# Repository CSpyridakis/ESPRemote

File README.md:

# ESPRemote
### VER 1.1

This repository is a fork of [Almidi's version of ESPRemote](https://github.com/Almidi/ESPRemote), a simple WiFI remote controller using the ESP8266 SoC.

The main difference between his implementation and this fork is about the limit of the input power supply voltage. In his repo, he uses an _[AP2112K](https://www.google.gr/url?sa=t&rct=j&q=&esrc=s&source=web&cd=1&ved=2ahUKEwjnxLrnpvbgAhUEK1AKHWMBD-AQFjAAegQIChAC&url=https%3A%2F%2Fwww.diodes.com%2Fassets%2FDatasheets%2FAP2112.pdf&usg=AOvVaw2XV2W1VE0JfD3LlF0lkARI)_ LDO voltage regulator that has a 6.5V Vin limit, to power it from USB chargers. 

Personally, I have all over in my place 12V power supplies to power led strips, for this reason, it would be a nice touch if I could power it directly from there without the need for an external power supply. So in this fork, the [NCP1117](https://www.onsemi.com/pub/Collateral/NCP1117-D.PDF) or [AMS1117](http://www.advanced-monolithic.com/pdf/ds1117.pdf) voltage regulator is used.

Please check out his [repo](https://github.com/Almidi/ESPRemote) if you want to use the battery/5v dc version, learn more about the beginning version or details about the firmware.

## PCB
### Schematic

#### Note: C3, C4, C5 and C6 are optional !!!

### Assembly
| No  |   Component   |    Quantity      |
|:---:|:-------------:|:----------------:|
| 1.  |      ESP8266 - 12e/f         | 1 | 
| 2.  |    10KΩ 0805 smd resistors   | 9 | 
| 3.  |      SMD-SWITCH-6.2MM        | 5 |
| 4.  |  IN5819 or SS14 or S4 Diode  | 1 |
| 5.  | NCP1117 or REG1117 Regulator | 1 |
| 6.  | 10uF 25v 0805 smd capasitors | 2 |
| 7.  |          0603 smd led        | 1 |
| 8.  |  0805 smd resistor for led <sup>1</sup>  | 1 |

<sup>1</sup> The resistor value depends on the color of the led you would choose to use.

### Top

### Bottom

## I/O

| Usage           | Pin    |
|-----------------|--------|
| Button 1        | GPIO5  |
| Button 2        | GPIO4  |
| Button 3        | GPIO12 |
| Button 4        | GPIO0  |
| Button 5        | GPIO13 |
| Status Led      | GPIO16 |

## Enclosure 
I also use [Almidi's](https://github.com/Almidi/ESPRemote) enclosure for this version.

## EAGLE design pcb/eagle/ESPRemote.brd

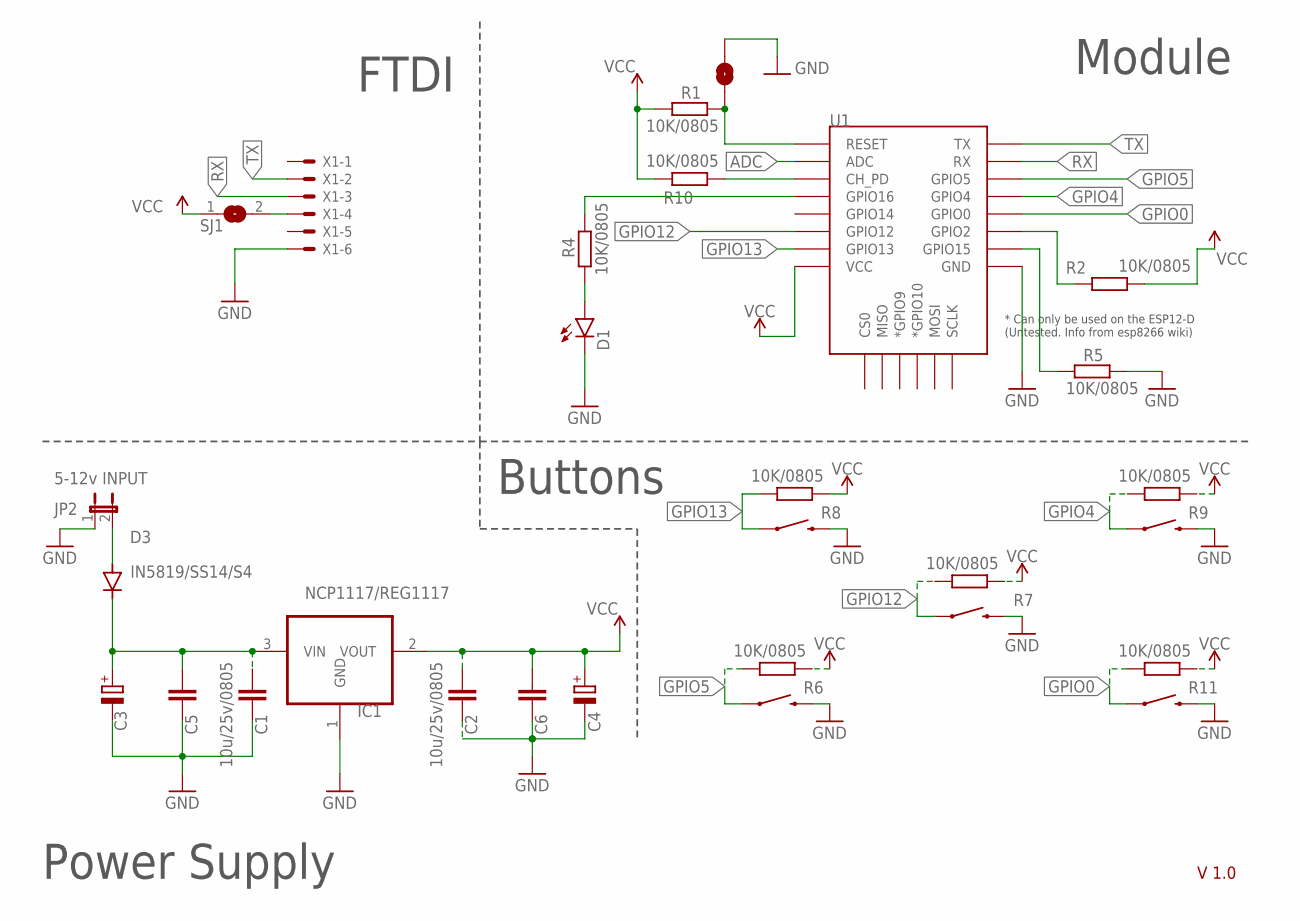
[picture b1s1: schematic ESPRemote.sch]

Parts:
C1, C2, C5, C6: 10u/25v/0805; C0805
C3, C4: CPOL-EUE2-5; E2-5
D1: BLUE; CHIP-LED0805
D3: IN5819/SS14/S4; DO-214AC
IC1: NCP1117/REG1117; SOT223
JP1: RST; SMT-JUMPER_2_NO_NO-SILK
JP2: 5-12v INPUT; JP1
R1, R2, R4, R5, R6, R7, R8, R9, R10, R11: 10K/0805; R0805
S0, S1, S2, S3, S4: SMD-SWITCH-6.2MM; TACTILE_SWITCH_SMD_6.0X3.5MM
SJ1: SJ
U1: ESP12ESMD; ESP12E-SMD
X1: JST-XH-06-PIN-ROUND-PAD; JST-XH-06-PACKAGE-ROUND-PAD

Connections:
ADC: U1.ADC
GND: C1.1, C2.1, C3.-, C4.-, C5.1, C6.1, D1.C, IC1.1 (GND), JP1.2, JP2.1, R5.2, S0.2, S1.2, S2.2, S3.2, S4.2, U1.GND, X1.6
GPIO0: R11.1, S4.1, U1.GPIO0
GPIO4: R9.1, S3.1, U1.GPIO4
GPIO5: R6.1, S2.1, U1.GPIO5
GPIO12: R7.1, S1.1, U1.GPIO12
GPIO13: R8.1, S0.1, U1.GPIO13
unnamed: C1.2, C3.+, C5.2, D3.C, IC1.3 (VIN)
unnamed: JP1.1, R1.2, U1.RESET
unnamed: D3.A, JP2.2
unnamed: R10.2, U1.CH_PD
unnamed: R2.1, U1.GPIO2
unnamed: SJ1.2, X1.4
unnamed: R5.1, U1.GPIO15
unnamed: R4.2, U1.GPIO16
unnamed: D1.A, R4.1
RX: U1.RXD0 (RX), X1.3
TX: U1.TXD0 (TX), X1.2
VCC: C2.2, C4.+, C6.2, IC1.2 (VOUT), R1.1, R2.2, R6.2, R7.2, R8.2, R9.2, R10.1, R11.2, SJ1.1, U1.VCC

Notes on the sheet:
Buttons
Module
FTDI
Power Supply
V 1.0

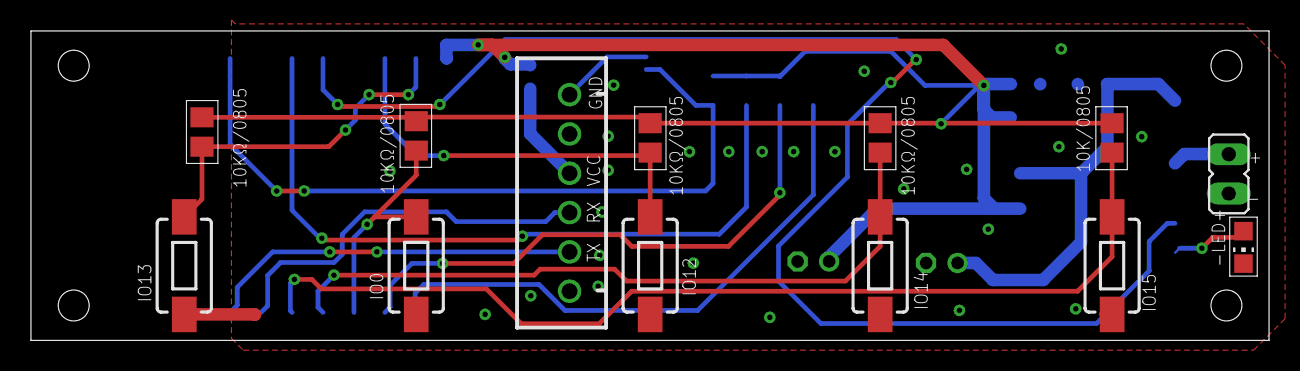
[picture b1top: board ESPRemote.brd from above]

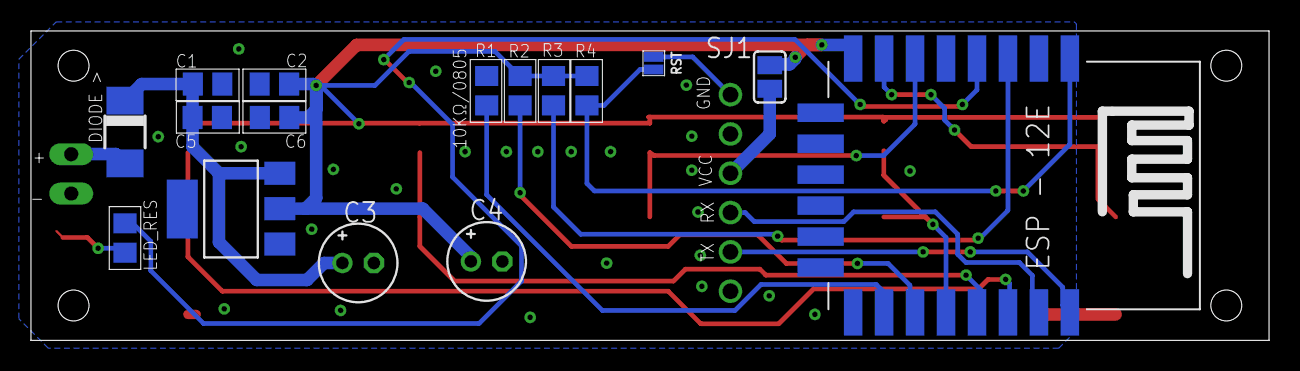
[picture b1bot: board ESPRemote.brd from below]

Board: 2 copper layers, 80.0 x 20.0 mm, 29 parts (16 on the bottom side), 18 nets.

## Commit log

2020-03-18 Ver.1.1 updated with 12V regulator
2020-03-18 Led's trace width updated
2020-03-19 Fix airwires
2020-03-20 Crop pcb images

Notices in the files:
parts and their libraries:
SparkFun-Switches: Licensing: Creative Commons ShareAlike 4.0 International - https://creativecommons.org/licenses/by-sa/4.0
